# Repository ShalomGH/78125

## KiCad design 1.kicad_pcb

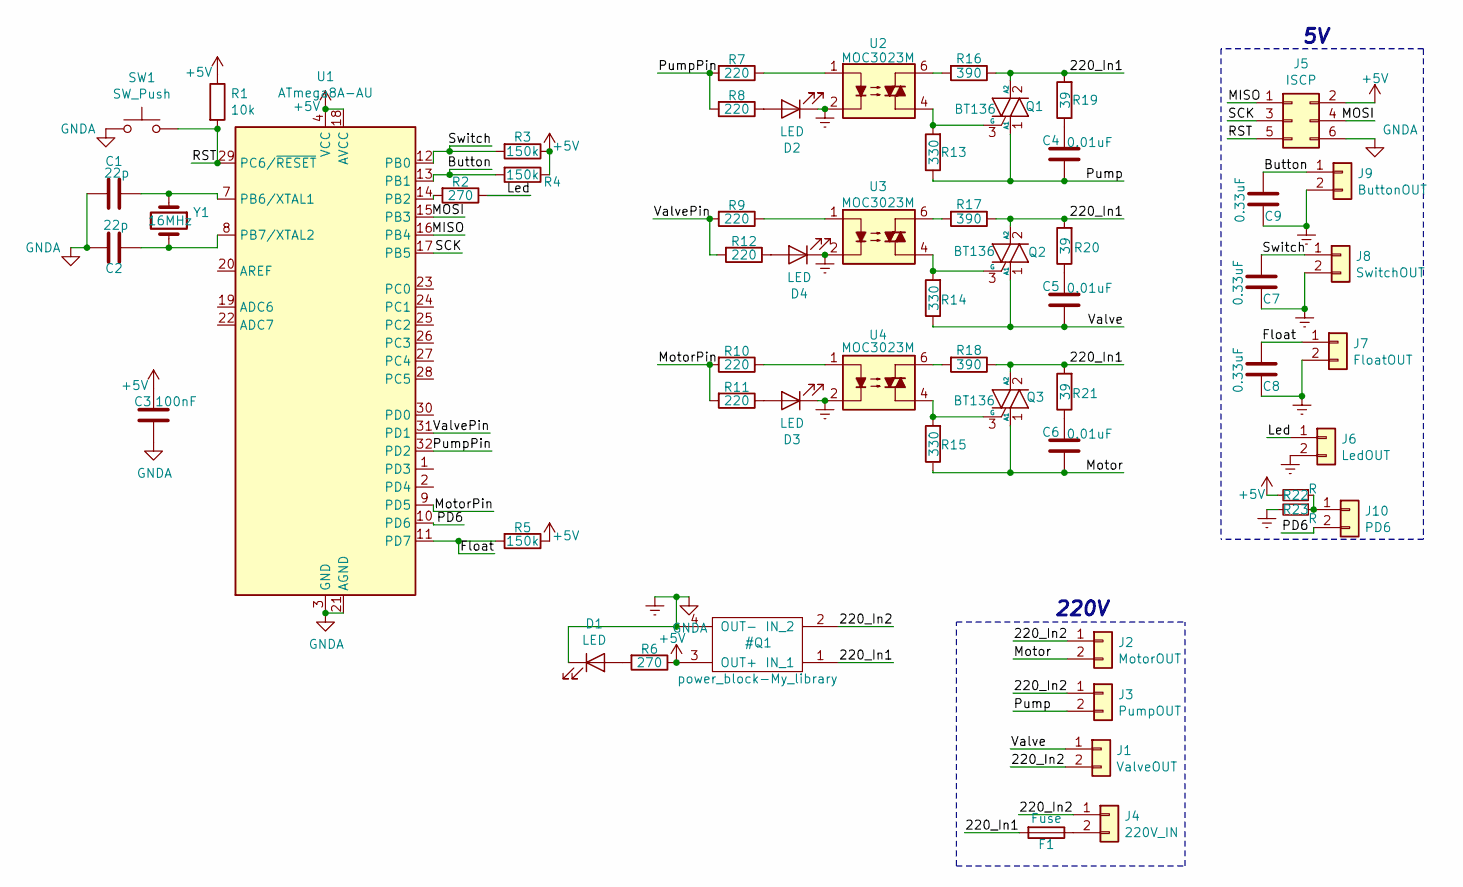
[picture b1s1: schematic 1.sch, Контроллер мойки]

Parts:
C1, C2: 22p; C_Disc_D3.8mm_W2.6mm_P2.50mm
C3: 100nF; C_0805_HandSoldering
C4, C5, C6: 0.01uF; C_Disc_D6.0mm_W4.4mm_P5.00mm
C7, C8, C9: 0.33uF; C_0805_HandSoldering
D1: LED; LED_1206_HandSoldering
D2, D3, D4: LED; LED_D3.0mm
F1: Fuse; MyBladeFuse
J1: ValveOUT; TerminalBlock_Altech_AK300-2_P5.00mm
J2: MotorOUT; TerminalBlock_Altech_AK300-2_P5.00mm
J3: PumpOUT; TerminalBlock_Altech_AK300-2_P5.00mm
J4: 220V_IN; TerminalBlock_Altech_AK300-2_P5.00mm
J5: ISCP; Pin_Header_Straight_2x03_Pitch2.54mm
J6: LedOUT; TerminalBlock_Altech_AK300-2_P5.00mm
J7: FloatOUT; TerminalBlock_Altech_AK300-2_P5.00mm
J8: SwitchOUT; TerminalBlock_Altech_AK300-2_P5.00mm
J9: ButtonOUT; TerminalBlock_Altech_AK300-2_P5.00mm
J10: PD6; TerminalBlock_Altech_AK300-2_P5.00mm
Q1, Q2, Q3: BT136; TO-220-3_Vertical
R1: 10k; R_1206
R2, R6: 270; R_1206
R3, R4, R5: 150k; R_1206
R7, R8, R9, R10, R11, R12: 220; R_1206
R13, R14, R15: 330; R_Axial_DIN0414_L11.9mm_D4.5mm_P15.24mm_Horizontal
R16, R17, R18: 390; R_Axial_DIN0414_L11.9mm_D4.5mm_P15.24mm_Horizontal
R19, R20, R21: 39; R_Axial_DIN0414_L11.9mm_D4.5mm_P15.24mm_Horizontal
R22, R23: R; R_0805
SW1: SW_Push; SW_PUSH_6mm
U1: ATmega8A-AU; LQFP-32_7x7mm_Pitch0.8mm
U2, U3, U4: MOC3023M; DIP-6_W7.62mm
Y1: 16MHz; Crystal_SMD_HC49-SD

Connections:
/Button: C9.1, J9.1, R4.2, U1.13 (PB1)
/Float: C8.1, J7.1, R5.2, U1.11 (PD7); also elsewhere on the board
/Led: J6.1, R2.1
/MISO: J5.1, U1.16 (PB4)
/MOSI: J5.4, U1.15 (PB3)
/Motor: C6.1, J2.2, Q3.1 (A1), R15.1
/MotorPin: R10.2, R11.2, U1.9 (PD5)
/PD6: J10.2, U1.10 (PD6)
/Pump: C4.1, J3.2, Q1.1 (A1), R13.1
/PumpPin: R7.2, R8.2, U1.32 (PD2)
/RST: J5.5, R1.2, SW1.2, U1.29 (PC6/~RESET)
/SCK: J5.3, U1.17 (PB5)
/Switch: C7.1, J8.1, R3.2, U1.12 (PB0)
/Valve: C5.1, J1.1, Q2.1 (A1), R14.1
/ValvePin: R9.2, R12.2, U1.31 (PD1)
unnamed: C1.1, U1.7 (PB6/XTAL1), Y1.1
unnamed: C2.1, U1.8 (PB7/XTAL2), Y1.2
unnamed: C4.2, R19.1
unnamed: C5.2, R20.1
unnamed: C6.2, R21.1
unnamed: D1.2 (A), R6.2
unnamed: D2.2 (A), R8.1
unnamed: D3.2 (A), R11.1
unnamed: D4.2 (A), R12.1
unnamed: F1.1, J4.2
unnamed 25: J10.1, R22.1, R23.1; also elsewhere on the board
unnamed: Q1.3 (G), R13.2, U2.4
unnamed: Q2.3 (G), R14.2, U3.4
unnamed: Q3.3 (G), R15.2, U4.4
unnamed: R2.2, U1.14 (PB2)
unnamed: R7.1, U2.1
unnamed: R9.1, U3.1
unnamed: R10.1, U4.1
unnamed: R16.2, U2.6
unnamed: R17.2, U3.6
unnamed: R18.2, U4.6

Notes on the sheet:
220V

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
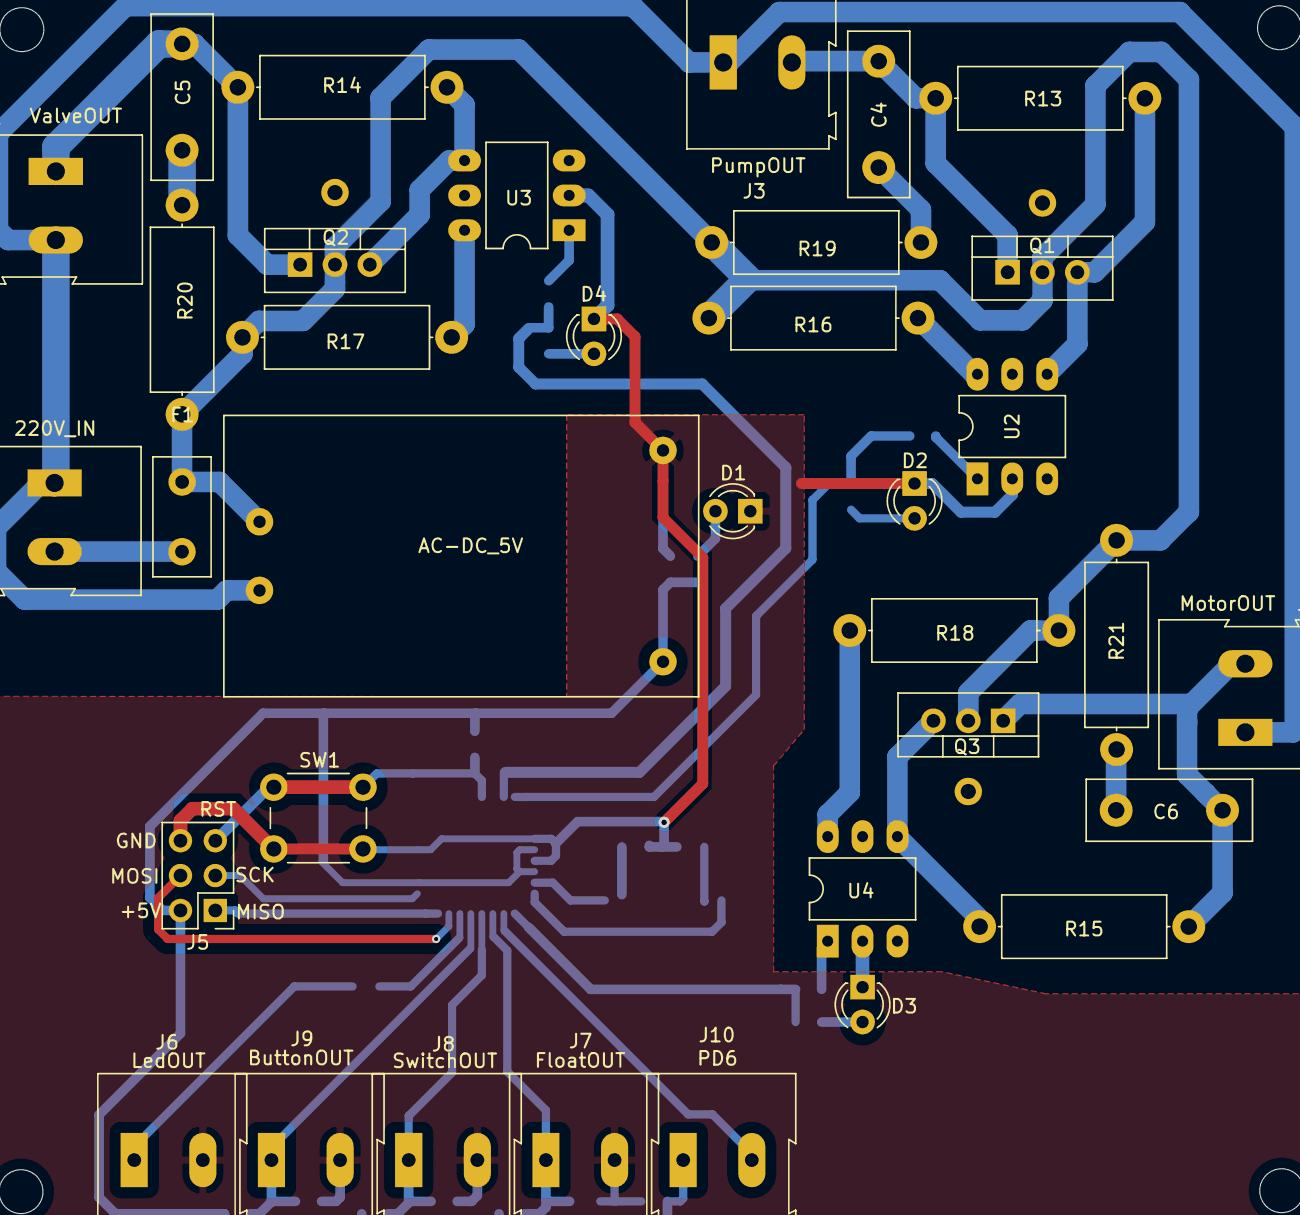
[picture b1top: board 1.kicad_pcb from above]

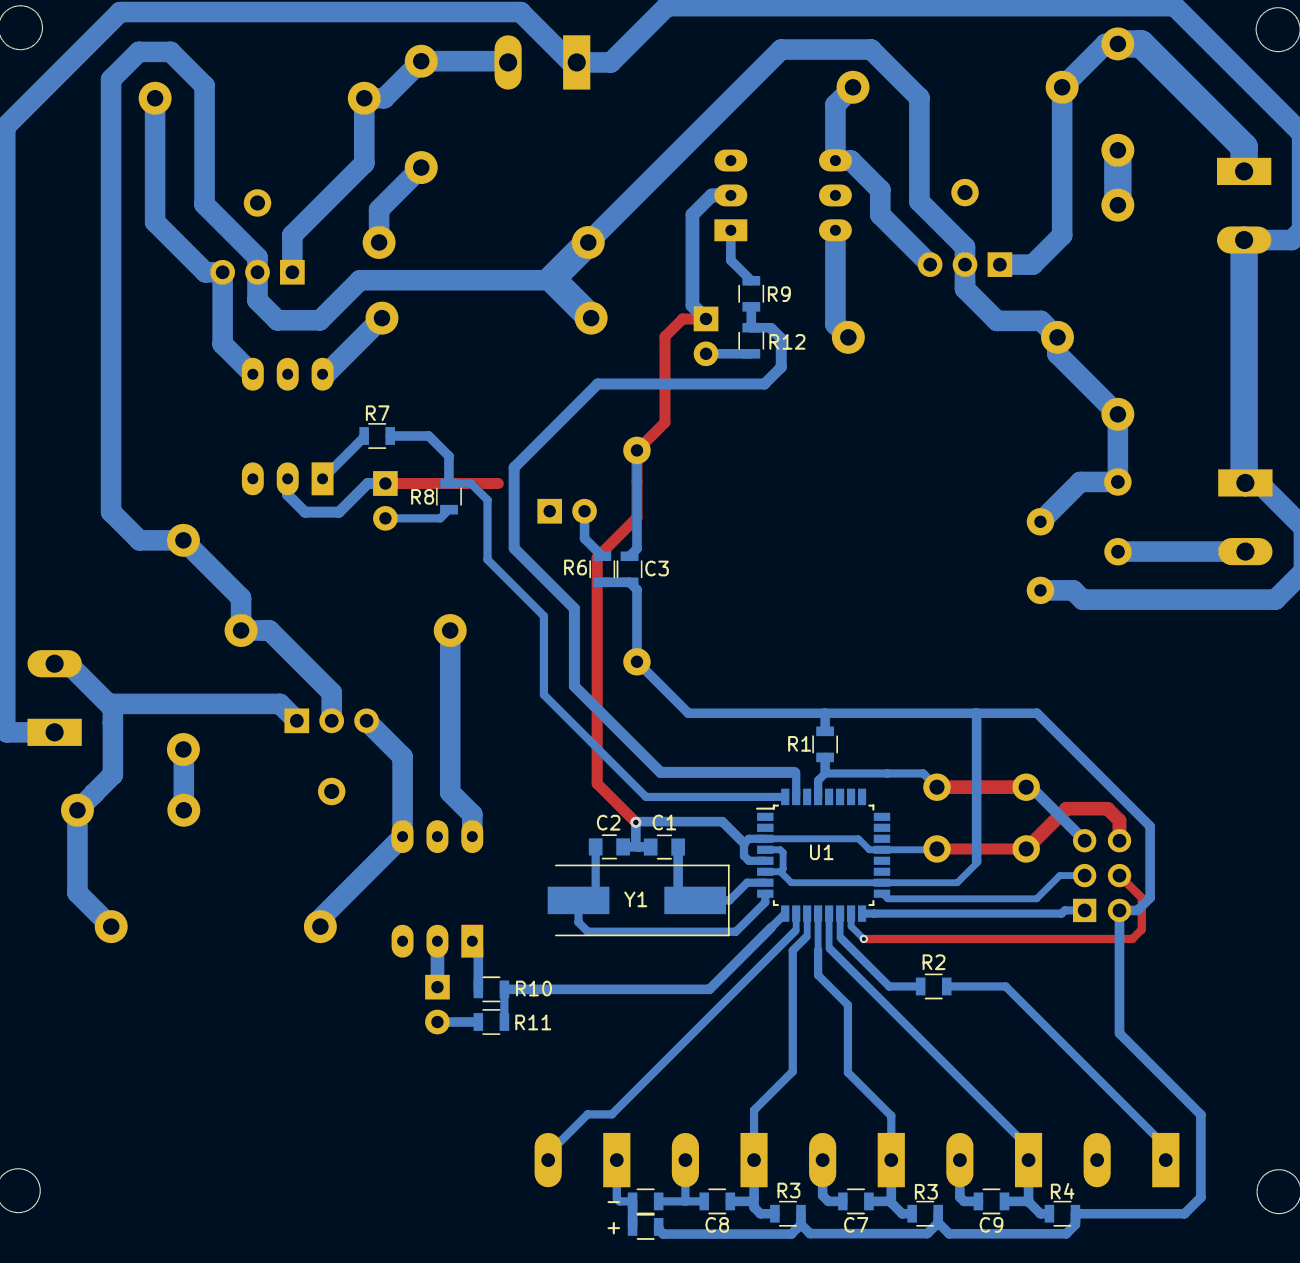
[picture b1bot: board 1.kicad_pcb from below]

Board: 2 copper layers, 57 parts (22 on the bottom side), 40 nets.

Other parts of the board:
+: R; R_0805
-: R; R_0805
AC-DC_5V: BP_12V; MINI_PB_GERM
R3#2: 150k; R_0805

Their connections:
/Float: R3#2.2; also elsewhere on the board
unnamed 25: +.1, -.1; also elsewhere on the board
